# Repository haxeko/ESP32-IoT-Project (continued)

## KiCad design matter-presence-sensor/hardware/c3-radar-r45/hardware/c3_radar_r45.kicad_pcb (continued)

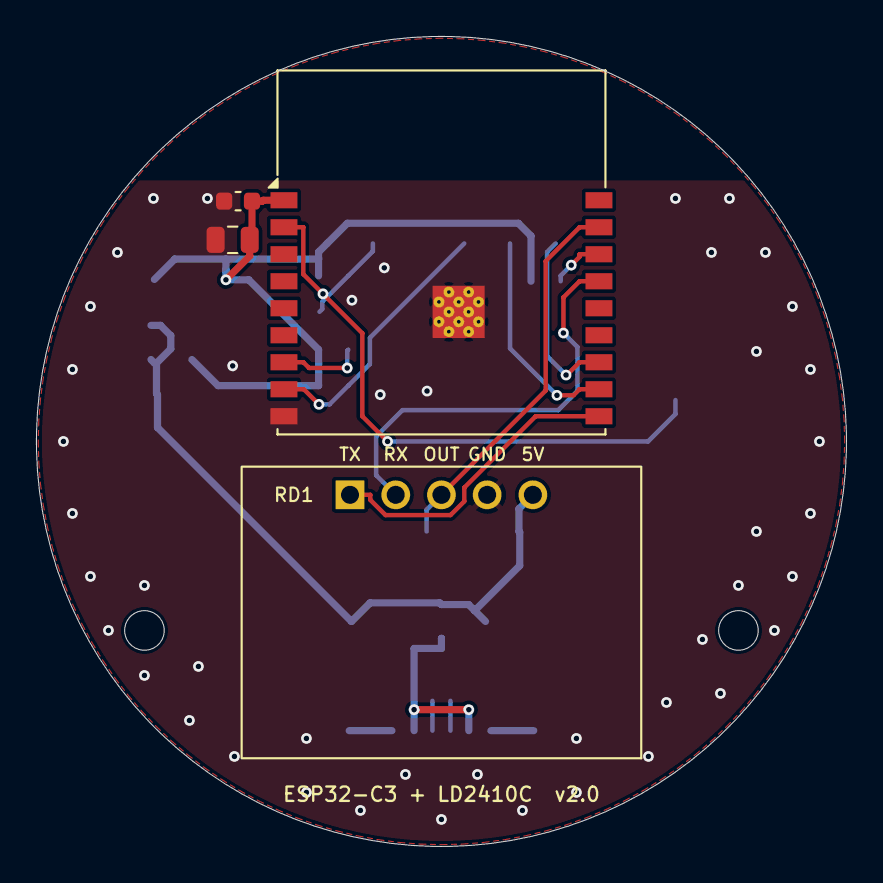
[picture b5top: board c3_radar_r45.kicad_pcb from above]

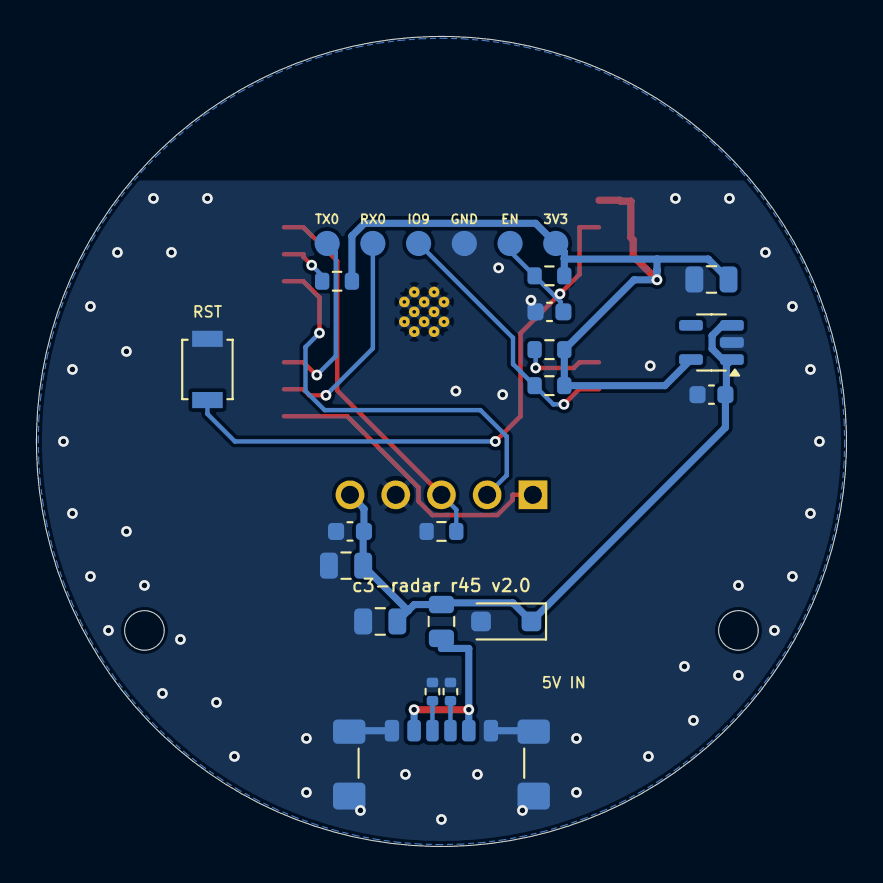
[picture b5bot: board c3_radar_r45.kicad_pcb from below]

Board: 2 copper layers, 45.0 x 45.0 mm, 30 parts (24 on the bottom side), 15 nets.

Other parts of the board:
H1, H2: M2; MountingHole_2.2mm_M2

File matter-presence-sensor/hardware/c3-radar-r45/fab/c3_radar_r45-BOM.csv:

References,Qty,Value,Footprint,Side,Part / note
C1,1,22uF,C_0805_2012Metric,bottom,MLCC X5R/X7R >=10 V
C8,1,100nF,C_0603_1608Metric,bottom,MLCC X5R/X7R >=10 V
C2,1,4.7uF,C_0603_1608Metric,bottom,"MLCC X5R/X7R >=10 V, LDO input (AP2112K needs >=1 uF at VIN)"
C3 C7,2,10uF,C_0805_2012Metric,bottom,MLCC X5R/X7R >=10 V
C4,1,10uF,C_0805_2012Metric,top,MLCC X5R/X7R >=10 V
C5,1,100nF,C_0603_1608Metric,top,MLCC X5R/X7R >=10 V
C6,1,1uF,C_0603_1608Metric,bottom,MLCC X5R/X7R >=10 V
D1,1,SMF5.0A,D_SOD-123F,bottom,"SMF5.0A TVS, SOD-123F/SOD-123FL"
F1,1,PTC 0.5A,Fuse_0805_2012Metric,bottom,"PTC resettable fuse 0805, Ihold 0.5 A, >=6 V"
J1,1,USB-C 6P (power only),USB_C_Receptacle_GCT_USB4135-GF-A_6P_TopMnt_Horizontal,bottom,GCT USB4135-GF-A or equivalent 6P SMD USB-C (check footprint!)
R1 R2,2,5.1k,R_0402_1005Metric,bottom,5.1k 1% 0402
R3 R4 R5 R6,4,10k,R_0603_1608Metric,bottom,
R7,1,100k,R_0603_1608Metric,bottom,
RD1,1,HLK-LD2410C,HLK-LD2410C_1x05_P2.54mm,top,"Hi-Link HLK-LD2410C (hand-soldered, header on the PCB)"
SW1,1,RESET,SW_SPST_B3U-1000P,bottom,Omron B3U-1000P
U1,1,ESP32-C3-WROOM-02-N4,ESP32-C3-WROOM-02,top,Espressif ESP32-C3-WROOM-02-N4
U2,1,AP2112K-3.3,SOT-23-5,bottom,"Diodes AP2112K-3.3TRG1 (alt: ME6211C33M5G, same pinout)"
H1 H2,2,M2 mounting hole,MountingHole_2.2mm_M2,-,"NPTH, no part"

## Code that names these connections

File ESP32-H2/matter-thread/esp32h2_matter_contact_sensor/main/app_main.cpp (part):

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 * ESP32-H2 Matter over Thread contact sensor (door / window sensor), powered from USB.
 *
 * Endpoint 0: Root Node. Endpoint 1: Contact Sensor (device type 0x0015) with the Identify and Boolean State
 * clusters. A reed switch between a GPIO and GND gives the door state.
 *
 * Start-up and structure follow esp-matter release/v1.6.1 examples/sensors, the closest official example
 * (that release has no contact sensor example). Changes from it:
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static_assert(!is_reserved_pin(CONFIG_FACTORY_RESET_GPIO),
              "FACTORY_RESET_GPIO is a flash or USB pin (GPIO6-7, GPIO15-21, GPIO26-27)");
static_assert(CONFIG_CONTACT_SENSOR_GPIO != CONFIG_FACTORY_RESET_GPIO,
              "The reed switch and the reset button need different GPIOs");
#if CONFIG_STATUS_LED_ENABLE
static_assert(!is_reserved_pin(CONFIG_STATUS_LED_GPIO) && CONFIG_STATUS_LED_GPIO != CONFIG_CONTACT_SENSOR_GPIO &&
                  CONFIG_STATUS_LED_GPIO != CONFIG_FACTORY_RESET_GPIO,
              "STATUS_LED_GPIO is a flash/USB pin or is shared with the reed switch or the button");
#endif

#if CONFIG_CONTACT_ACTIVE_LOW
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    return state == CONTACT_STATE_CLOSED;
}

// The whole chain from the pin, for CONFIG_CONTACT_ACTIVE_LOW=y (default, normally-open reed switch to GND):
//   GPIO LOW  (magnet at the switch, contact closed) -> CONTACT_STATE_CLOSED -> StateValue true
//   GPIO HIGH (magnet away, pull-up)                 -> CONTACT_STATE_OPEN   -> StateValue false
// CONFIG_CONTACT_ACTIVE_LOW=n swaps the two GPIO levels.
static bool reed_level_to_matter_state(int level)
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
